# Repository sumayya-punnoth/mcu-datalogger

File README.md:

# MCU Datalogger

4 layer PCB design of a datalogger using Atmega 328P-AU in KiCad.

## Viewing the project
1. Clone the repository:
```bash
git clone https://github.com/sumayya-punnoth/mcu-datalogger
```
2. Open `mcu_datalogger.kicad_pro` to view the schematic and PCB layout.

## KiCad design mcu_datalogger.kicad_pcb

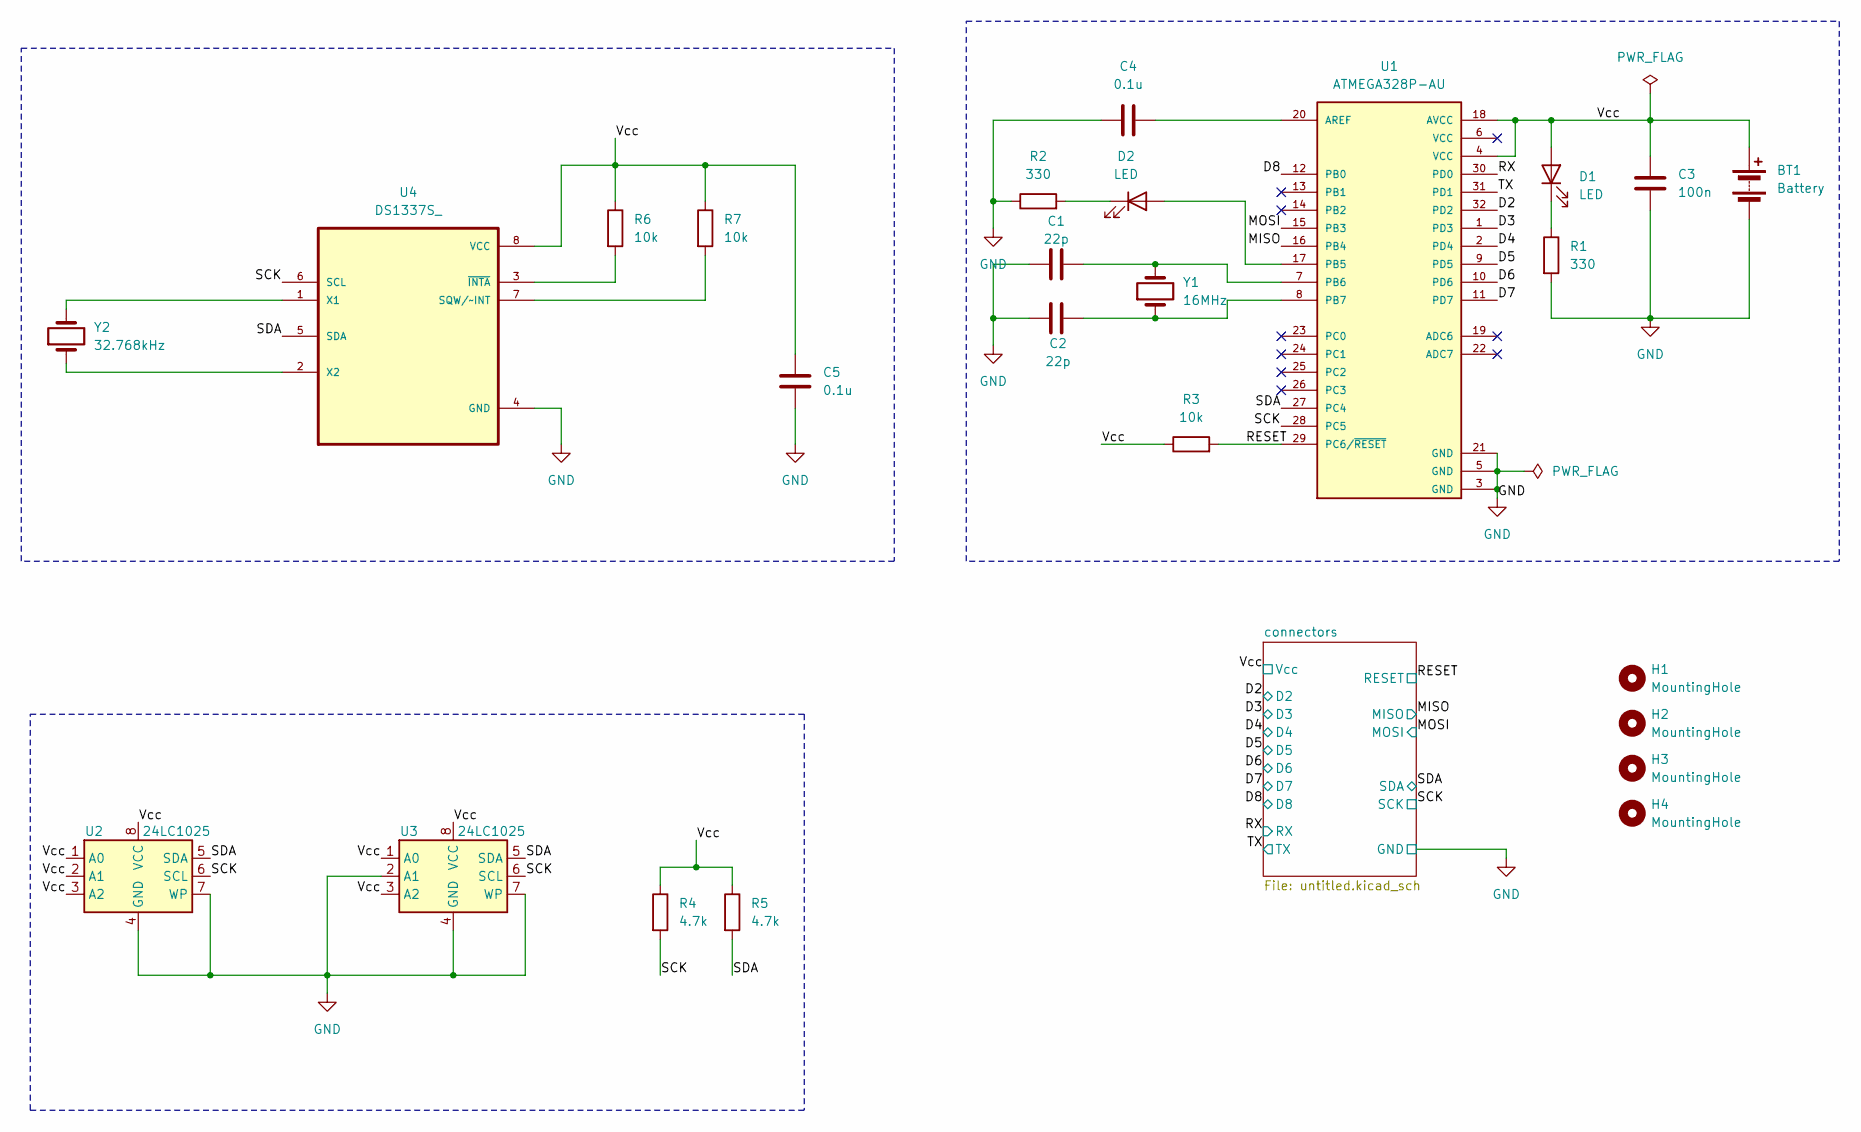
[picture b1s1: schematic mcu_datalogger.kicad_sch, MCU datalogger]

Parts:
BT1: Battery; PinHeader_1x02_P2.54mm_Vertical
C1, C2: 22p; C_0805_2012Metric
C3: 100n; C_0805_2012Metric
C4, C5: 0.1u; C_0805_2012Metric
D1, D2: LED; LED_0805_2012Metric
H1, H2, H3, H4: MountingHole; MountingHole_2.1mm
R1, R2: 330; R_0805_2012Metric
R3, R6, R7: 10k; R_0805_2012Metric
R4, R5: 4.7k; R_0805_2012Metric
U1: ATMEGA328P-AU; QFP80P900X900X120-32N; PARTREV 8271A; DigiKey_Part_Number ATMEGA328P-AU-ND
U2, U3: 24LC1025; SOIC-8_3.9x4.9mm_P1.27mm
U4: DS1337S_; SOIC127P600X175-8N
Y1: 16MHz; Crystal_SMD_5032-2Pin_5.0x3.2mm_HandSoldering
Y2: 32.768kHz; Crystal_SMD_5032-2Pin_5.0x3.2mm_HandSoldering

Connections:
/D2: U1.32 (PD2); also elsewhere on the board
/D3: U1.1 (PD3); also elsewhere on the board
/D4: U1.2 (PD4); also elsewhere on the board
/D5: U1.9 (PD5); also elsewhere on the board
/D6: U1.10 (PD6); also elsewhere on the board
/D7: U1.11 (PD7); also elsewhere on the board
/D8: U1.12 (PB0); also elsewhere on the board
/MISO: U1.16 (PB4); also elsewhere on the board
/MOSI: U1.15 (PB3); also elsewhere on the board
/RESET: R3.2, U1.29 (PC6/~RESET); also elsewhere on the board
/RX: U1.30 (PD0); also elsewhere on the board
/SCK: R4.2, U1.28 (PC5), U2.6 (SCL), U3.6 (SCL), U4.6 (SCL); also elsewhere on the board
/SDA: R5.2, U1.27 (PC4), U2.5 (SDA), U3.5 (SDA), U4.5 (SDA); also elsewhere on the board
/TX: U1.31 (PD1); also elsewhere on the board
/Vcc: BT1.1 (+), C3.1, C5.1, D1.2 (A), R3.1, R4.1, R5.1, R6.1, R7.1, U1.4 (VCC), U1.18 (AVCC), U2.1 (A0), U2.2 (A1), U2.3 (A2), U2.8 (VCC), U3.1 (A0), U3.3 (A2), U3.8 (VCC), U4.8 (VCC); also elsewhere on the board
GND: BT1.2 (-), C1.1, C2.1, C3.2, C4.1, C5.2, R1.2, R2.1, U1.3 (GND), U1.5 (GND), U1.21 (GND), U2.4 (GND), U2.7 (WP), U3.2 (A1), U3.4 (GND), U3.7 (WP), U4.4 (GND); also elsewhere on the board
unnamed: D1.1 (K), R1.1
unnamed: D2.2 (A), U1.17 (PB5)
unnamed: D2.1 (K), R2.2
unnamed: C4.2, U1.20 (AREF)
unnamed: C1.2, U1.7 (PB6), Y1.2
unnamed: C2.2, U1.8 (PB7), Y1.1
unnamed: R7.2, U4.7 (SQW/~INT)
unnamed: U4.1 (X1), Y2.2
unnamed: U4.2 (X2), Y2.1
unnamed: R6.2, U4.3 (~INTA)

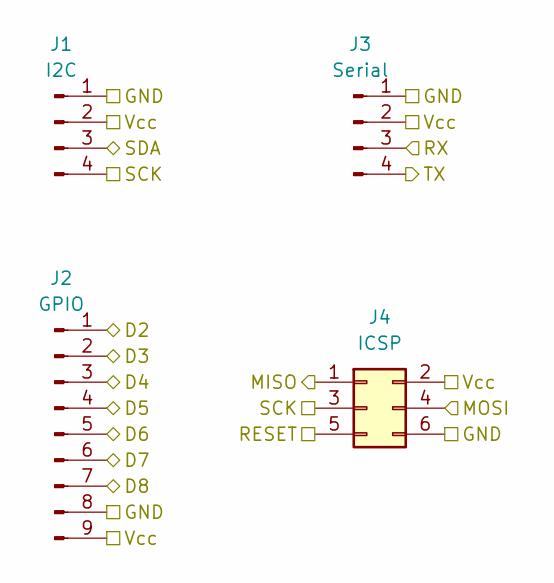
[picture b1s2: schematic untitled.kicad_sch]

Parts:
J1: I2C; PinHeader_1x04_P2.54mm_Vertical
J2: GPIO; PinHeader_1x09_P2.54mm_Vertical
J3: Serial; PinHeader_1x04_P2.54mm_Vertical
J4: ICSP; PinHeader_2x03_P2.54mm_Vertical

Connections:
/D2: J2.1; also elsewhere on the board
/D3: J2.2; also elsewhere on the board
/D4: J2.3; also elsewhere on the board
/D5: J2.4; also elsewhere on the board
/D6: J2.5; also elsewhere on the board
/D7: J2.6; also elsewhere on the board
/D8: J2.7; also elsewhere on the board
/MISO: J4.1; also elsewhere on the board
/MOSI: J4.4; also elsewhere on the board
/RESET: J4.5; also elsewhere on the board
/RX: J3.3; also elsewhere on the board
/SCK: J1.4, J4.3; also elsewhere on the board
/SDA: J1.3; also elsewhere on the board
/TX: J3.4; also elsewhere on the board
/Vcc: J1.2, J2.9, J3.2, J4.2; also elsewhere on the board
GND: J1.1, J2.8, J3.1, J4.6; also elsewhere on the board

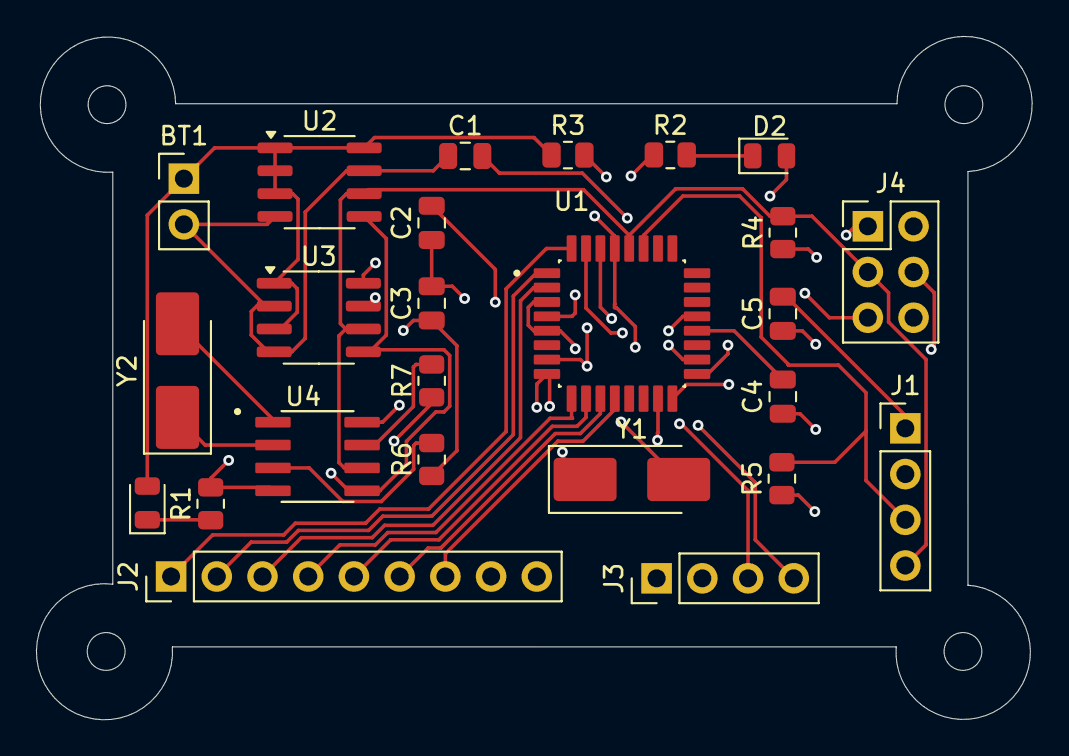
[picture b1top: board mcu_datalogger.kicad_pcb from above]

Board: 4 copper layers, 55.3 x 38.0 mm, 29 parts (0 on the bottom side), 26 nets.
